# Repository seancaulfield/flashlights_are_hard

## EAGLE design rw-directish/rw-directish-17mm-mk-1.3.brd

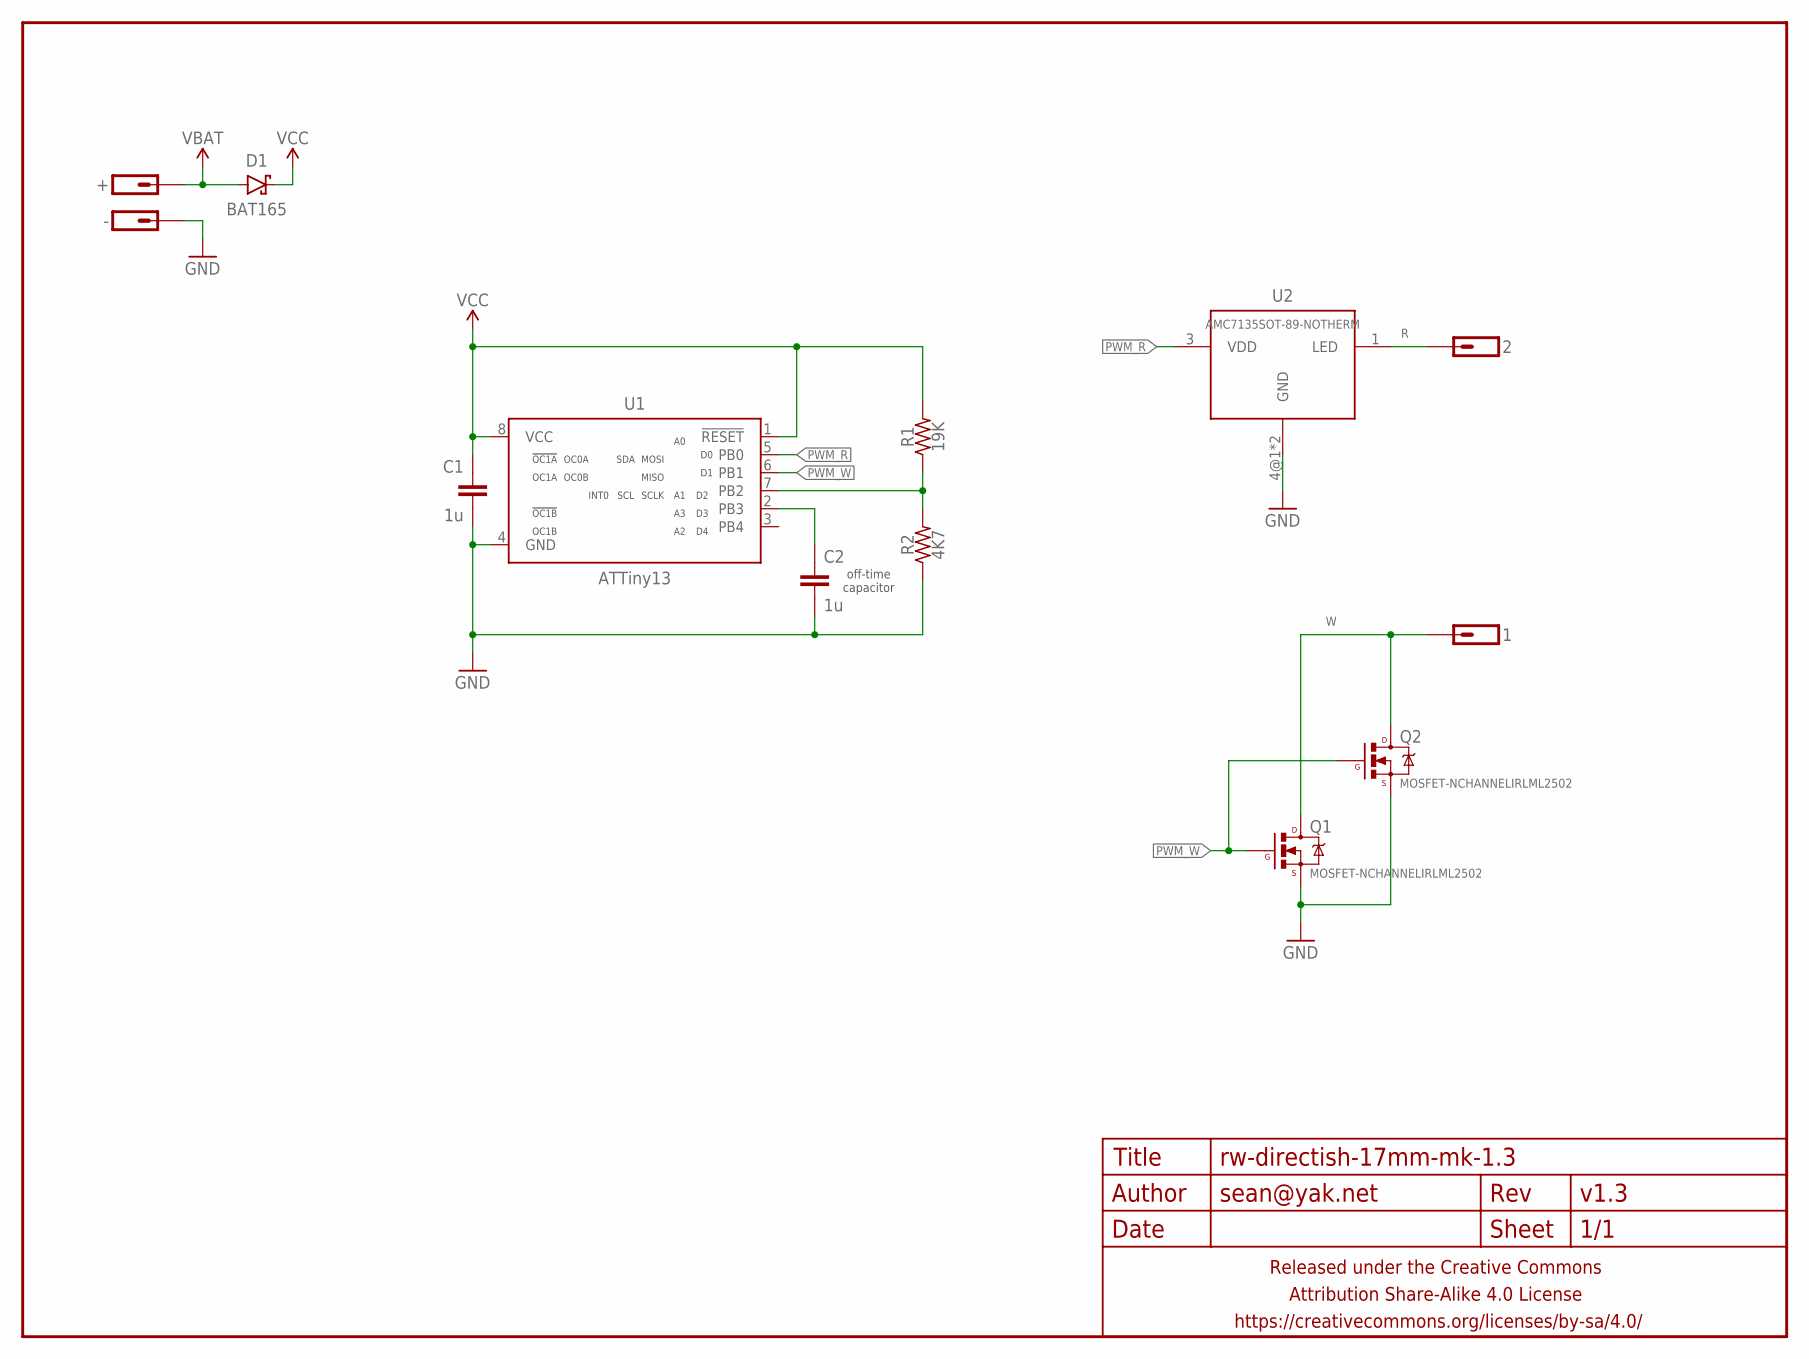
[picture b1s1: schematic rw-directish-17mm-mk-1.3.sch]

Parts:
1, 2: M01SMD-1.25MM-DIA; 1X01-SMD-1.25MM-DIA-NS
+: M01PTH-1MM-CIR-NS; 1X01-1MM-CIR-NS
-: M01NOT-A-VIA-NOPE; 1X01_NOSILK_NOSTOP
C1, C2: 1u; C0603-TIGHTER
D1: BAT165; SOD323-SCHOTTKY
FRAME1: FRAME-LETTERNO_PACKAGE; DUMMY
Q1, Q2: MOSFET-NCHANNELIRLML2502; SOT23
R1: 19K; R0603-TIGHTER
R2: 4K7; R0603-TIGHTER
U1: ATTiny13; SO08-NARROWER
U2: AMC7135SOT-89-NOTHERM; SOT89-NOTHERM

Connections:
GND: -.P$1, C1.2, C2.2, Q1.2 (S), Q2.2 (S), R2.1, U1.4 (GND), U2.4@1 (GND), U2.4@2 (GND)
unnamed: R1.1, R2.2, U1.7 (PB2)
unnamed: C2.1, U1.2 (PB3)
PWM_R: U1.5 (PB0), U2.3 (VDD)
PWM_W: Q1.1 (G), Q2.1 (G), U1.6 (PB1)
R: 2.P$1, U2.1 (LED)
VBAT: +.1, D1.A
VCC: C1.1, D1.C, R1.2, U1.1 (!RESET), U1.8 (VCC)
W: 1.P$1, Q1.3 (D), Q2.3 (D)

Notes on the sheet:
off-time capacitor

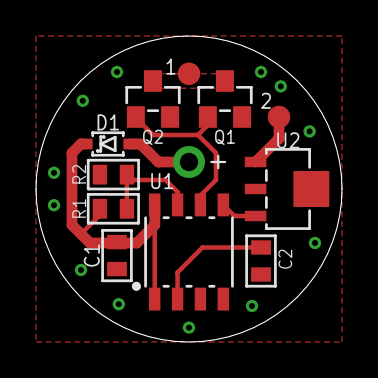
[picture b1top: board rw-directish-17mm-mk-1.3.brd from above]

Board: 2 copper layers, 17.0 x 17.0 mm, 14 parts (1 on the bottom side), 9 nets.

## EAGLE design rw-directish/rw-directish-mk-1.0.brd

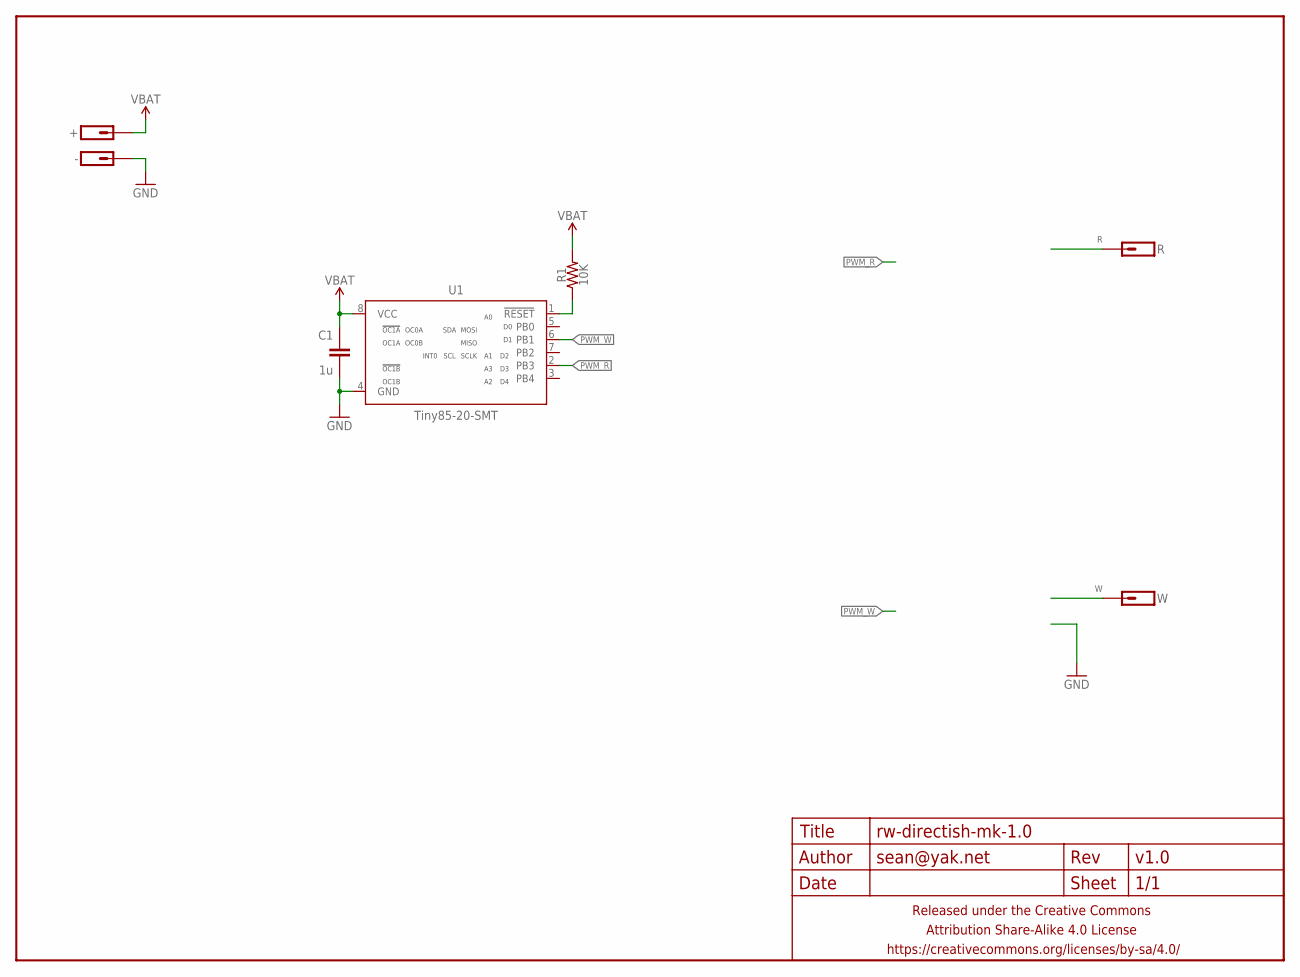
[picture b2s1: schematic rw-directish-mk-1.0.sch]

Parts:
+: M01PTH-1.2MM-NS; 1X01-1.2MM-NS
-: M01NOT-A-VIA-NOPE; 1X01_NOSILK_NOSTOP
C1: 1u; C0402
FRAME1: FRAME-LETTERNO_PACKAGE; DUMMY
R: M01SMD-1.25MM-DIA; 1X01-SMD-1.25MM-DIA-NS
R1: 10K; R0402
U1: Tiny85-20-SMT; SO08-EIAJ
W: M01SMD-1.25MM-DIA; 1X01-SMD-1.25MM-DIA-NS

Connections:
GND: -.P$1, C1.2, U1.4 (GND)
unnamed: R1.1, U1.1 (!RESET)
PWM_R: U1.2 (PB3)
PWM_W: U1.6 (PB1)
R: R.P$1
VBAT: +.P$1, C1.1, R1.2, U1.8 (VCC)
W: W.P$1

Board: 2 copper layers, 8 parts (1 on the bottom side), 3 nets, no tracks yet.

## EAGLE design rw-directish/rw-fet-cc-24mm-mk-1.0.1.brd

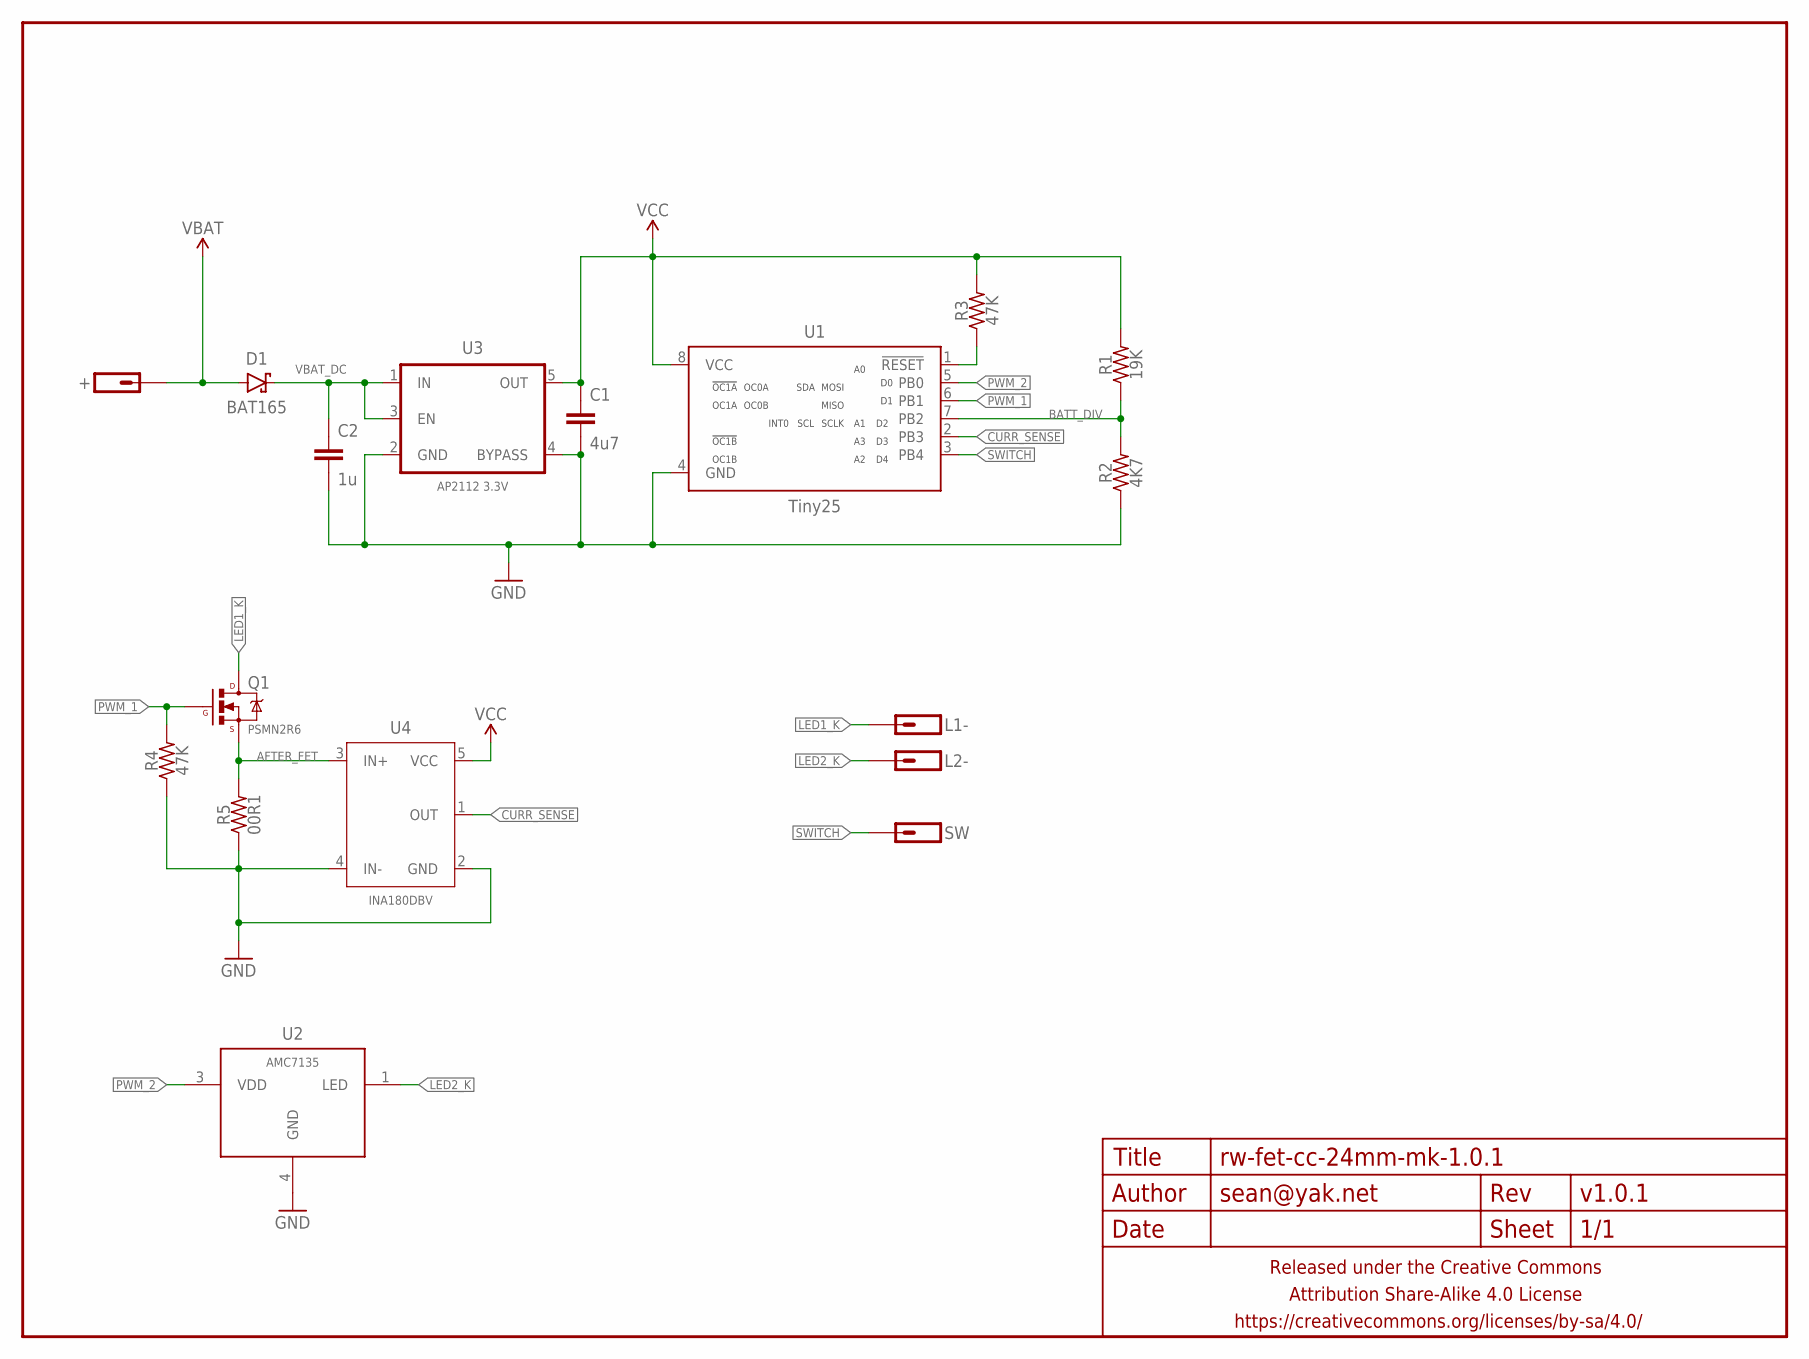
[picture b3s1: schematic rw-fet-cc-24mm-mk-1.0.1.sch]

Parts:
+: M01PTH-1MM-CIR-NS; 1X01-1MM-CIR-NS
C1: 4u7; C0603-TIGHTER
C2: 1u; C0402
D1: BAT165; SOD323-SCHOTTKY
FRAME1: FRAME-LETTERNO_PACKAGE; DUMMY
L1-: M011X01-0.9MM-CIR; 1X01-0.9MM-CIR
L2-: M01PTH-0.8MM-CIR; 1X01-0.8MM-CIR
Q1: PSMN2R6; POWERPACK-SO-8
R1: 19K; R0402
R2: 4K7; R0402
R3, R4: 47K; R0402
R5: 00R1; R1206
SW: M01SMD-0.8MM-DIA-NS; 1X01-SMD-0.8MM-DIA-NS
U1: Tiny25; SO08-NARROWER
U2: AMC7135; SOT89-NOTHERM-ROUNDED-LESS
U3: AP2112 3.3V; SOT23-5
U4: INA180DBV; SOT23-5

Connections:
AFTER_FET: Q1.1 (S), Q1.2 (S), Q1.3 (S), R5.2, U4.3 (IN+)
BATT_DIV: R1.1, R2.2, U1.7 (PB2)
CURR_SENSE: U1.2 (PB3), U4.1 (OUT)
GND: C1.2, C2.2, R2.1, R4.1, R5.1, U1.4 (GND), U2.4 (GND), U3.2 (GND), U3.4 (BYPASS), U4.2 (GND), U4.4 (IN-)
LED1_K: L1-.P$1, Q1.5678 (D)
LED2_K: L2-.1, U2.1 (LED)
unnamed: R3.1, U1.1 (!RESET)
PWM_1: Q1.4 (G), R4.2, U1.6 (PB1)
PWM_2: U1.5 (PB0), U2.3 (VDD)
SWITCH: SW.P$1, U1.3 (PB4)
VBAT: +.1, D1.A
VBAT_DC: C2.1, D1.C, U3.1 (IN), U3.3 (EN)
VCC: C1.1, R1.2, R3.2, U1.8 (VCC), U3.5 (OUT), U4.5 (VCC)

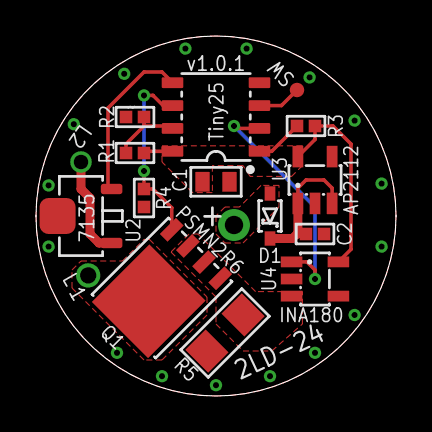
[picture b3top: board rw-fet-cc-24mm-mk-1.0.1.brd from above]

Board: 2 copper layers, 20.0 x 20.0 mm, 18 parts (0 on the bottom side), 13 nets.

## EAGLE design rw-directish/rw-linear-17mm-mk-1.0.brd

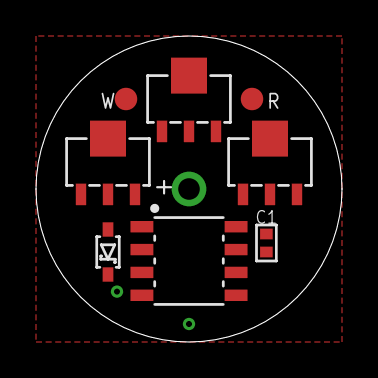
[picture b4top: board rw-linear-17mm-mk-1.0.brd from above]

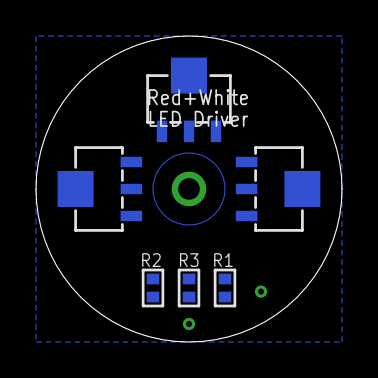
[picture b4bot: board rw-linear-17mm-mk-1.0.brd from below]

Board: 2 copper layers, 17.0 x 17.0 mm, 17 parts (7 on the bottom side), 9 nets, no tracks yet.

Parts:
+: M01PTH-1.2MM-NS; 1X01-1.2MM-NS
-: M01NOT-A-VIA-NOPE; 1X01_NOSILK_NOSTOP
C1: 1u; C0402
D1: BAT165; SOD323-SCHOTTKY
FRAME1: FRAME-LETTERNO_PACKAGE; DUMMY
R: M01SMD-1.25MM-DIA; 1X01-SMD-1.25MM-DIA-NS
R1: 10K; R0402
R2: 19K; R0402
R3: 4K7; R0402
U1: SO08-NARROWER
U2, U3, U4, U5, U6, U7: AMC7135; SOT89-NOTHERM
W: M01SMD-1.25MM-DIA; 1X01-SMD-1.25MM-DIA-NS

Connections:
BATT_DIV: R2.1, R3.2, U1.7
GND: -.P$1, C1.2, R3.1, U1.4, U2.4@1, U2.4@2, U3.4@1, U3.4@2, U4.4@1, U4.4@2, U5.4@1, U5.4@2, U6.4@1, U6.4@2, U7.4@1, U7.4@2
unnamed: R1.1, U1.1
PWM_R: U1.5, U5.3, U6.3, U7.3
PWM_W: U1.6, U2.3, U3.3, U4.3
RED_K: R.P$1, U5.1, U6.1, U7.1
VBAT: +.P$1, D1.A
VCC: C1.1, D1.C, R1.2, R2.2, U1.8
WHITE_K: U2.1, U3.1, U4.1, W.P$1

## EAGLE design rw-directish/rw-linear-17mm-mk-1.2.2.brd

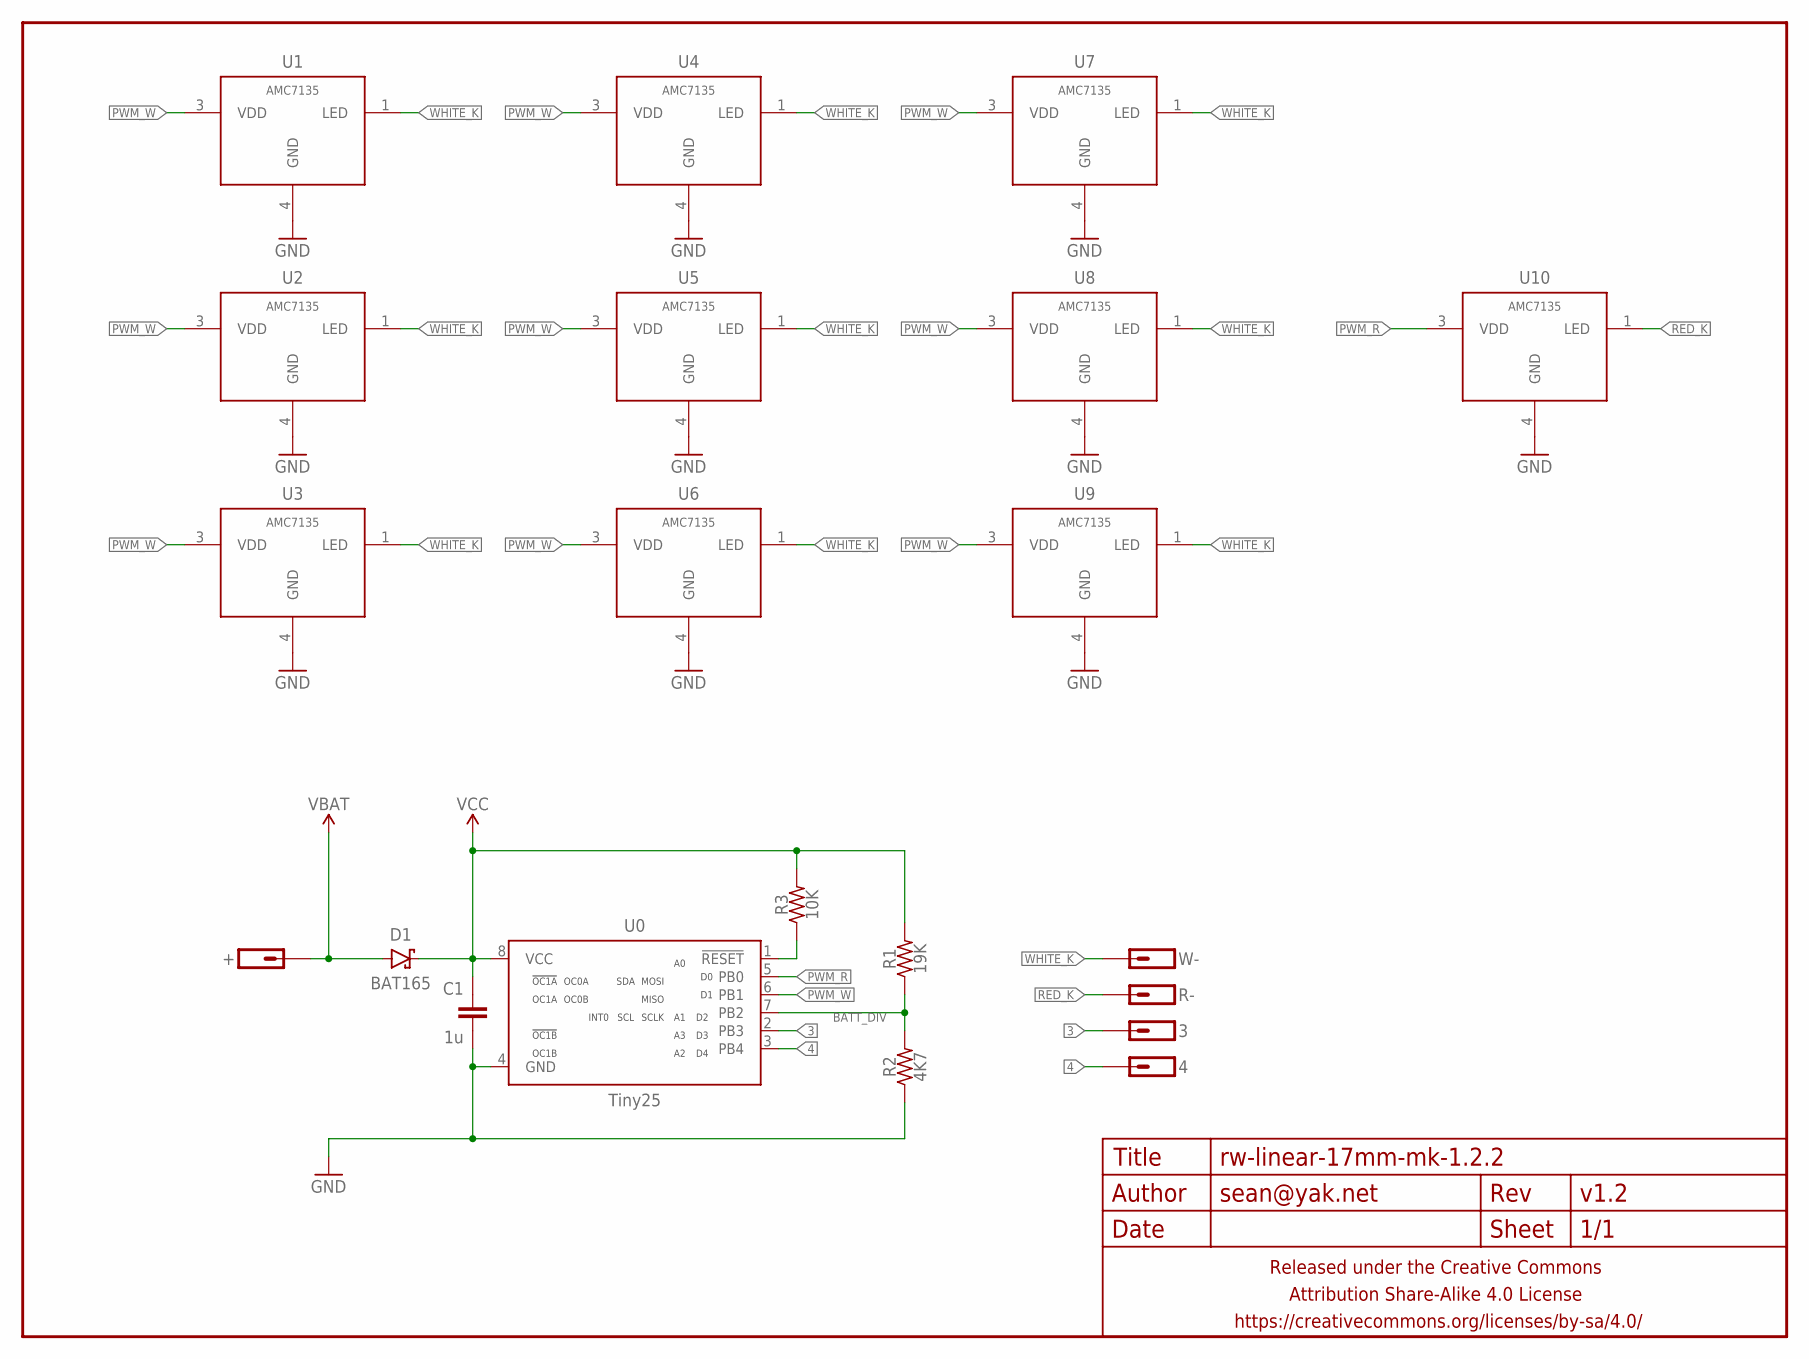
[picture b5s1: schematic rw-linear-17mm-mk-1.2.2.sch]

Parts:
3, 4: M01SMD-1MM-DIA-NS; 1X01-SMD-1MM-DIA-NS
+: M01PTH-1.2MM-NS; 1X01-1.2MM-NS
C1: 1u; C0402
D1: BAT165; SOD323-SCHOTTKY
FRAME1: FRAME-LETTERNO_PACKAGE; DUMMY
R1: 19K; R0402
R2: 4K7; R0402
R3: 10K; R0402
R-: M01SMD-1.25MM-DIA; 1X01-SMD-1.25MM-DIA-NS
U0: Tiny25; SO08-NARROWER
U1, U2, U3, U4, U5, U6, U7, U8, U9, U10: AMC7135; SOT89-NOTHERM-ROUNDED-LESS
W-: M01SMD-1.5MM-DIA-NS; 1X01-SMD-1.5MM-DIA-NS

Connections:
3: 3.P$1, U0.2 (PB3)
4: 4.P$1, U0.3 (PB4)
BATT_DIV: R1.1, R2.2, U0.7 (PB2)
GND: C1.2, R2.1, U0.4 (GND), U1.4 (GND), U2.4 (GND), U3.4 (GND), U4.4 (GND), U5.4 (GND), U6.4 (GND), U7.4 (GND), U8.4 (GND), U9.4 (GND), U10.4 (GND)
unnamed: R3.1, U0.1 (!RESET)
PWM_R: U0.5 (PB0), U10.3 (VDD)
PWM_W: U0.6 (PB1), U1.3 (VDD), U2.3 (VDD), U3.3 (VDD), U4.3 (VDD), U5.3 (VDD), U6.3 (VDD), U7.3 (VDD), U8.3 (VDD), U9.3 (VDD)
RED_K: R-.P$1, U10.1 (LED)
VBAT: +.P$1, D1.A
VCC: C1.1, D1.C, R1.2, R3.2, U0.8 (VCC)
WHITE_K: U1.1 (LED), U2.1 (LED), U3.1 (LED), U4.1 (LED), U5.1 (LED), U6.1 (LED), U7.1 (LED), U8.1 (LED), U9.1 (LED), W-.P$1

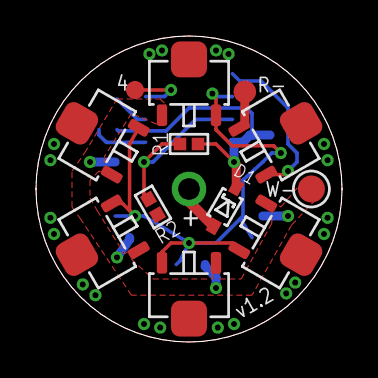
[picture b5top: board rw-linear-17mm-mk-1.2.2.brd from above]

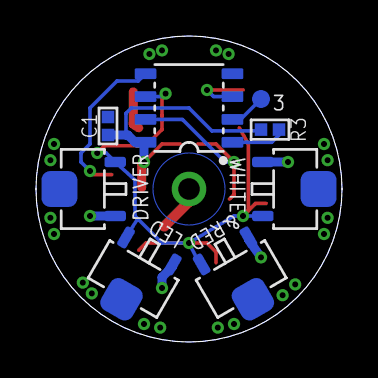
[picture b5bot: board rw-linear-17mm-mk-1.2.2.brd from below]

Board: 2 copper layers, 17.0 x 17.0 mm, 22 parts (8 on the bottom side), 11 nets.

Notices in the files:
parts and their libraries:
a_parts: Released under the Creative Commons Attribution Share-Alike 4.0 License
a_parts: https://creativecommons.org/licenses/by-sa/4.0
a_parts: Released under the Creative Commons
